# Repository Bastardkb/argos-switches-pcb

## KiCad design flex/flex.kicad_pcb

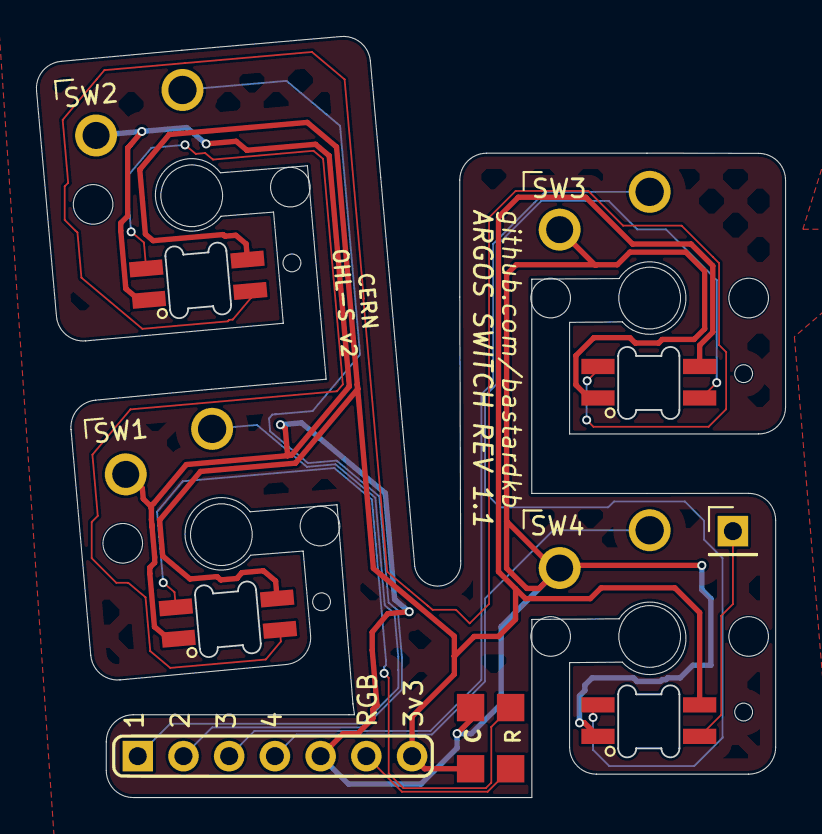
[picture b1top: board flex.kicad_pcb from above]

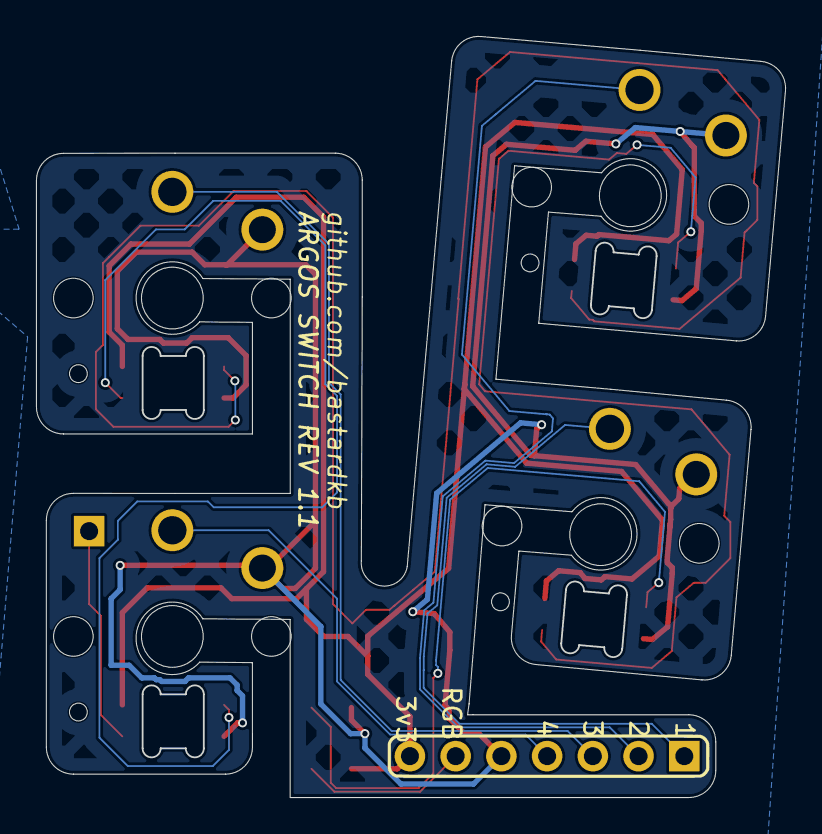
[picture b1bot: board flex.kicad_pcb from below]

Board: 2 copper layers, 41.6 x 42.3 mm, 12 parts (4 on the bottom side), 12 nets.

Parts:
C3: NA_C; C_SOD123
D13, D14, D15, D16: RIGHT_LED; SK6812_mini_e_corners
J2: Conn_01x01_Socket; PinHeader_1x01_P2.54mm_Vertical
J7: Conn_01x07_Socket; PinHeader_1x07_P2.54mm_Vertical
R3: NA_R; R_SOD123
SW5, SW6, SW7, SW8: SW_Push; choc

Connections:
Din: J7.6, R3.1
Gnd: C3.2, D13.2 (VSS), D14.2 (VSS), D15.2 (VSS), D16.2 (VSS), J7.5, SW5.2, SW6.2, SW7.2, SW8.2
unnamed: D13.3 (DIN), R3.2
unnamed: D13.1 (DOUT), D14.3 (DIN)
unnamed: D14.1 (DOUT), D15.3 (DIN)
unnamed: D15.1 (DOUT), D16.3 (DIN)
unnamed: D16.1 (DOUT), J2.1
Vcc: C3.1, D13.4 (VDD), D14.4 (VDD), D15.4 (VDD), D16.4 (VDD), J7.7
sw1: J7.1, SW6.1
sw2: J7.2, SW5.1
sw3: J7.3, SW8.1
sw4: J7.4, SW7.1

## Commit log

2024-06-20 move over
2024-06-20 switch numbering
2024-06-20 cleanup
